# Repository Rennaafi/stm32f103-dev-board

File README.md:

# STM32F103 Minimal Development Board

A compact 2-layer STM32F103 (LQFP-48) breakout board designed in **KiCad 9**. It is powered over USB and exposes SWD, SPI and I2C on pin headers.

## Features

- **MCU:** STM32F103 in LQFP-48 (U1)
- **Clock:** 16 MHz crystal (TSX-3225) with 8 pF load capacitors
- **Power:** USB Micro-B → AMS1117-3.3 LDO → 3.3 V, with a ferrite bead (120 Ω) filtering VDDA
- **USB:** D+ pull-up (1k5) on PA12
- **Boot mode:** slide switch (SW2) on BOOT0
- **Reset:** tactile button (SW1) on NRST
- **Power LED:** red LED (D1)
- **Headers:**
  - `J1`: SWD (3V3, SWDIO, SWCLK, GND)
  - `J3`: SPI1 (3V3, NSS, SCK, MISO, MOSI, GND)
  - `J4`: I2C1 on PB10/PB11 with 1k5 pull-ups
- **Board:** about 33.5 × 24.2 mm, 2 layers, 1.6 mm thick, all components on the top side

## Schematic

## PCB Layout

## Repository Structure

```
.
├── stm32f103_Muhammad Refansa Annaafi.kicad_pro   # KiCad project
├── stm32f103_Muhammad Refansa Annaafi.kicad_sch   # Schematic
├── stm32f103_Muhammad Refansa Annaafi.kicad_pcb   # PCB layout
├── Gerber/    # Fabrication outputs (Gerbers, drill files, job file)
├── BOM/       # Bill of materials (CSV)
└── Media/     # Screenshots and renders
```

## Bill of Materials

| Ref | Value | Footprint | Qty |
|---|---|---|---|
| U1 | STM32F103 | LQFP-48_7x7mm_P0.5mm | 1 |
| U2 | AMS1117-3.3 | SOT-223-3 | 1 |
| Y1 | 16 MHz crystal | TSX-3225 | 1 |
| J2 | USB Micro-B | Würth 629105150521 | 1 |
| FB1 | 120 Ω ferrite bead | BLM18PG121SN1D (0603) | 1 |
| C1–C4, C6, C10 | 100 nF | 0603 | 6 |
| C5, C11, C12 | 10 µF | 0603 | 3 |
| C7 | 1 µF | 0603 | 1 |
| C8, C9 | 8 pF | 0603 | 2 |
| R1 | 10 kΩ | 0603 | 1 |
| R3, R4, R5 | 1.5 kΩ | 0603 | 3 |
| R2 | 1 kΩ (LED resistor) | 0603 | 1 |
| D1 | Red LED | 0603 | 1 |
| SW1 | Tactile switch | 434133025816 | 1 |
| SW2 | SPDT slide switch | PCM12 | 1 |
| J1, J4 | 1×4 header | 1.00 mm pitch | 2 |
| J3 | 1×6 header | 1.00 mm pitch | 1 |

The full BOM is in [`BOM/`](BOM).

## Manufacturing

Upload the contents of [`Gerber/`](Gerber) to a PCB fab such as JLCPCB or PCBWay. It includes the copper, mask, paste, silkscreen and edge-cut layers, plus the PTH/NPTH drill files.

## Opening the Project

Open the `.kicad_pro` file in KiCad 9.0 or newer. The project uses a custom `KCCI` symbol/footprint library for some parts (for example the crystal). If those parts show up as missing, add that library to your library tables.

## Author

Muhammad Refansa Annaafi. Designed as part of the KCCI PCB design training.

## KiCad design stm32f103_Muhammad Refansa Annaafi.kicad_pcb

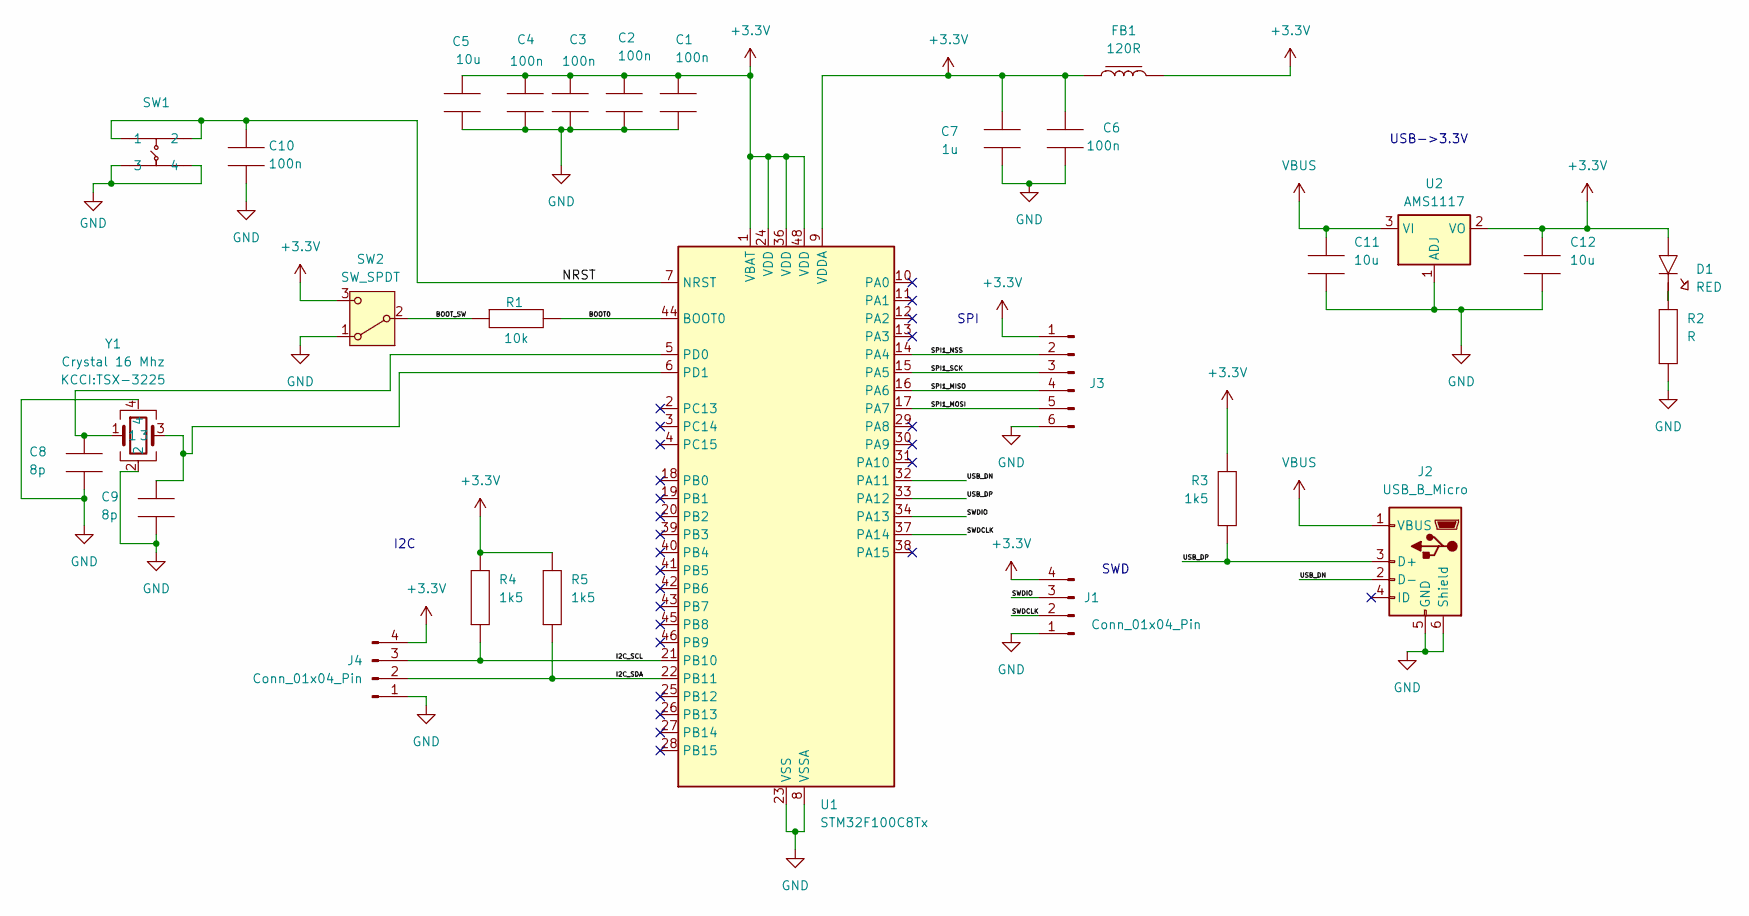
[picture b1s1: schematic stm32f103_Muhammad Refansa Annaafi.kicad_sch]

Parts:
C1, C2, C3, C4, C6, C10: 100n; C_0603_
C5, C11, C12: 10u; C_0603_
C7: 1u; C_0603_
C8, C9: 8p; C_0603_
D1: RED; LED_0603_1608Metric
FB1: 120R; BLM18PG121SN1D
J1, J4: Conn_01x04_Pin; PinHeader_1x04_P1.00mm_Vertical
J2: USB_B_Micro; USB_Micro-B_Wuerth_629105150521
J3: Conn_01x06_Pin; PinHeader_1x06_P1.00mm_Vertical
R1: 10k; R_0603
R2: R; R_0603
R3, R4, R5: 1k5; R_0603
SW1: button_434133025816
SW2: SW_SPDT; SW_SPDT_PCM12
U1: STM32F100C8Tx; LQFP-48_7x7mm_P0.5mm
U2: AMS1117; SOT-223-3_TabPin2
Y1: Crystal 16 Mhz; TSX-3225

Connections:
+3.3V: C1.2, C2.2, C3.2, C4.2, C5.2, C6.2, C7.2, C12.2, D1.1 (A), FB1.1, FB1.2, J1.4, J3.1, J4.4, R3.2, R4.2, R5.2, SW2.3 (C), U1.1 (VBAT), U1.9 (VDDA), U1.24 (VDD), U1.36 (VDD), U1.48 (VDD), U2.2 (VO)
/BOOT0: R1.2, U1.44 (BOOT0)
/BOOT_SW: R1.1, SW2.2 (B)
/I2C_SCL: J4.3, R4.1, U1.21 (PB10)
/I2C_SDA: J4.2, R5.1, U1.22 (PB11)
/NRST: C10.2, SW1.1, SW1.2, U1.7 (NRST)
/SPI1_MISO: J3.4, U1.16 (PA6)
/SPI1_MOSI: J3.5, U1.17 (PA7)
/SPI1_NSS: J3.2, U1.14 (PA4)
/SPI1_SCK: J3.3, U1.15 (PA5)
/SWDCLK: J1.2, U1.37 (PA14)
/SWDIO: J1.3, U1.34 (PA13)
/USB_DN: J2.2 (D-), U1.32 (PA11)
/USB_DP: J2.3 (D+), R3.1, U1.33 (PA12)
GND: C1.1, C2.1, C3.1, C4.1, C5.1, C6.1, C7.1, C8.1, C9.1, C10.1, C11.1, C12.1, J1.1, J2.5 (GND), J2.6 (Shield), J3.6, J4.1, R2.1, SW1.3, SW1.4, SW2.1 (A), U1.8 (VSSA), U1.23 (VSS), U1.35 (VSS), U1.47 (VSS), U2.1 (ADJ), Y1.2, Y1.4
unnamed: D1.2 (C), R2.2
unnamed: C8.2, U1.5 (PD0), Y1.1
unnamed: C9.2, U1.6 (PD1), Y1.3
VBUS: C11.2, J2.1 (VBUS), U2.3 (VI)

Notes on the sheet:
SPI
I2C
USB->3.3V
SWD

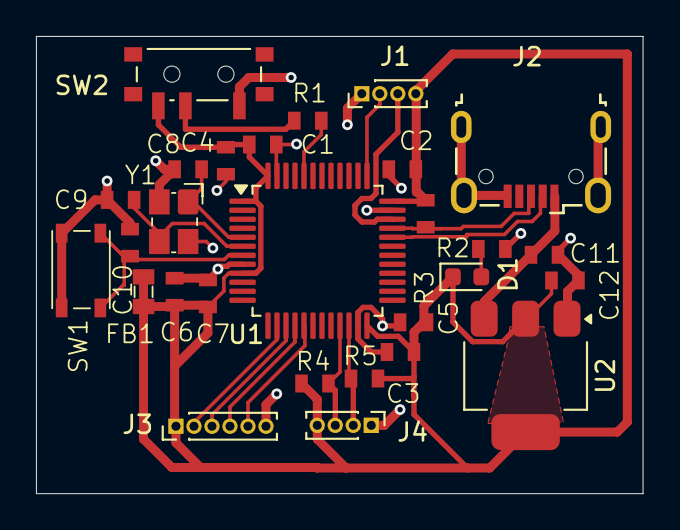
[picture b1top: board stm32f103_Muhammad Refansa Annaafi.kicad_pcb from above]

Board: 2 copper layers, 33.7 x 25.4 mm, 28 parts (0 on the bottom side), 19 nets.
